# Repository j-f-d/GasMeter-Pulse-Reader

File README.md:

# GasMeter Pulse Reader

This project was forked from https://github.com/optoisolated/GasMeter-Pulse-Reader with the intention of providing the correct MQTT topics, such that it will work with the MQTT integration for https://www.home-assistant.io/ with the minimum of fuss.

I use a nodemocuv2 for monitoring at the moment, rather than the hardware created by @MakerMeik and @optoisolated so the pin I use is different (GPIO14 on D5 instead of GPIO9 or GPIO3). If you want to make the hardware, then you'll need to change this.

The mosquitto server is "mosquitto.home" and the device will look for that name using the DNS server provided by the DHCP configuration. The credentials used are stored in your secrets.h file. I add an entry in my DNS server, such that mosquitto.home redirects to the server which is running the mosquitto service.

The homeassistant MQTT integration is configured for the same server and when reloaded should see a new gas_meter device, which provides 2 entities. The gas_consumption entity is suitable for use with the energy dash board. The gas_flow_rate entity I use to determine how much gas is being used at any given moment.

This schematic and PCB layout will allow you to build, read, tally and report on a standard Pulse-Type Gas and Water Meters. Each trigger event consists of 10L of Gas consumed. This device has been confirmed compatible with the following meters:

* Gameco Model 750 Gas Meter (10L/impulse)

This project was forked from MakerMeik's Gasmeter_with_reed project and has been updated to be completely self-contained, self-powered (or direct powered) and has hardware debounce using a Schmitt trigger.

Here you will find all the files you need to build ESP-01 microcontroller and a reed switch to read your Krom-Schröder gas meter electronically.  

## Links
* MakerMeik's original Project video: https://youtu.be/i9hPf0uNzFE
* Thingiverse - 3D-Model of the case: https://www.thingiverse.com/thing:5338232

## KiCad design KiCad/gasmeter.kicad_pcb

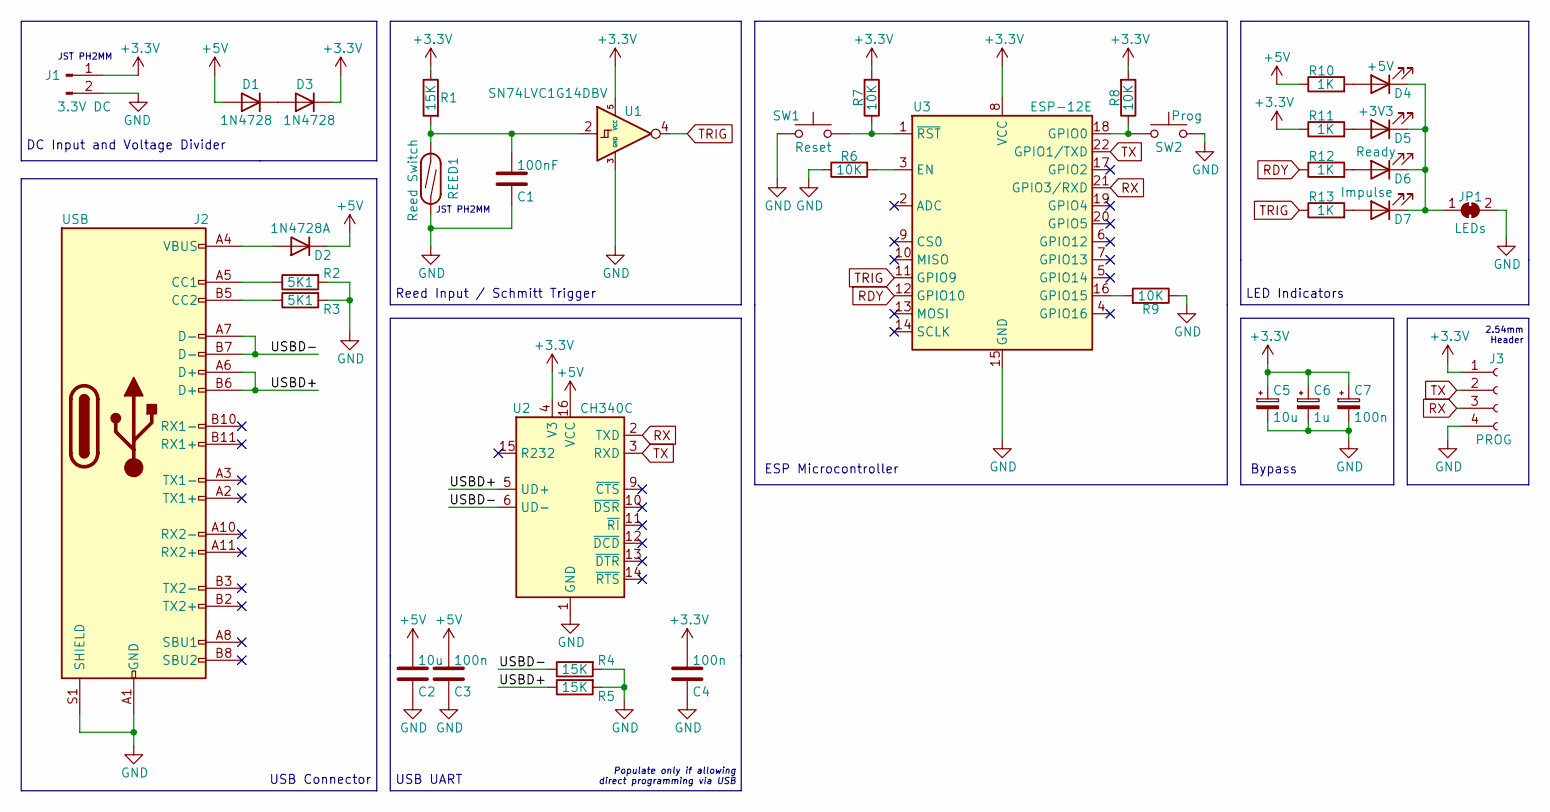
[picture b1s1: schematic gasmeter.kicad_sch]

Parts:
C1: 100nF; C_0805_2012Metric_Pad1.18x1.45mm_HandSolder
C2, C5: 10u; C_0805_2012Metric_Pad1.18x1.45mm_HandSolder
C3, C4, C7: 100n; C_0805_2012Metric_Pad1.18x1.45mm_HandSolder
C6: 1u; C_0805_2012Metric_Pad1.18x1.45mm_HandSolder
D1, D3: 1N4728; D_0805_2012Metric_Pad1.15x1.40mm_HandSolder
D2: 1N4728A; D_0805_2012Metric_Pad1.15x1.40mm_HandSolder
D4: +5V; LED_0805_2012Metric_Pad1.15x1.40mm_HandSolder
D5: +3V3; LED_0805_2012Metric_Pad1.15x1.40mm_HandSolder
D6: Ready; LED_0805_2012Metric_Pad1.15x1.40mm_HandSolder
D7: Impulse; LED_0805_2012Metric_Pad1.15x1.40mm_HandSolder
J1: 3.3V DC; JST_PH_B2B-PH-K_1x02_P2.00mm_Vertical
J2: USB; USB_C_Receptacle_Amphenol_12401548E4-2A
J3: PROG; PinHeader_1x04_P2.54mm_Vertical
JP1: LEDs; SolderJumper-2_P1.3mm_Bridged_Pad1.0x1.5mm
R1, R4, R5: 15K; R_0805_2012Metric_Pad1.20x1.40mm_HandSolder
R2, R3: 5K1; R_0805_2012Metric_Pad1.20x1.40mm_HandSolder
R6, R7, R8, R9: 10K; R_0805_2012Metric_Pad1.20x1.40mm_HandSolder
R10, R11, R12, R13: 1K; R_0805_2012Metric_Pad1.20x1.40mm_HandSolder
REED1: Reed Switch; JST_PH_B2B-PH-K_1x02_P2.00mm_Vertical
SW1: Reset; SW_SPST_EVQP2
SW2: Prog; SW_SPST_EVQP2
U1: SN74LVC1G14DBV; SOT-23-5
U2: CH340C; SOIC-16_3.9x9.9mm_P1.27mm
U3: ESP-12E

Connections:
+3V3: C4.2, C5.1, C6.1, C7.1, D3.1 (K), J1.1, J3.1, R1.1, R7.2, R8.2, R11.1, U1.5 (VCC), U2.4 (V3), U3.8 (VCC)
/USBD+: J2.A6 (D+), J2.B6 (D+), R5.1, U2.5 (UD+)
/USBD-: J2.A7 (D-), J2.B7 (D-), R4.1, U2.6 (UD-)
GND: C1.1, C2.1, C3.1, C4.1, C5.2, C6.2, C7.2, J1.2, J2.A1 (GND), J2.A12 (GND), J2.B1 (GND), J2.B12 (GND), J2.S1 (SHIELD), J3.4, JP1.2 (B), R2.2, R3.2, R4.2, R5.2, R6.1, R9.1, REED1.1, SW1.1, SW2.2, U1.3 (GND), U2.1 (GND), U3.15 (GND)
unnamed: C1.2, R1.2, REED1.2, U1.2
unnamed: D1.1 (K), D3.2 (A)
unnamed: D4.1 (K), D5.1 (K), D6.1 (K), D7.1 (K), JP1.1 (A)
unnamed: D4.2 (A), R10.2
unnamed: D5.2 (A), R11.2
unnamed: D6.2 (A), R12.2
unnamed: D7.2 (A), R13.2
unnamed: J2.A5 (CC1), R2.1
unnamed: J2.B5 (CC2), R3.1
unnamed: R6.2, U3.3 (EN)
unnamed: R7.1, SW1.2, U3.1 (~RST)
unnamed: R8.1, SW2.1, U3.18 (GPIO0)
unnamed: R9.2, U3.16 (GPIO15)
RDY: R12.1, U3.12 (GPIO10)
RX: J3.3, U2.2 (TXD), U3.21 (GPIO3/RXD)
TRIG: R13.1, U1.4, U3.11 (GPIO9)
TX: J3.2, U2.3 (RXD), U3.22 (GPIO1/TXD)

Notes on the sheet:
LED Indicators
JST PH2MM
USB Connector
Reed Input / Schmitt Trigger
ESP Microcontroller
2.54mm Header
DC Input and Voltage Divider
USB UART
Populate only if allowing direct programming via USB
Bypass

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
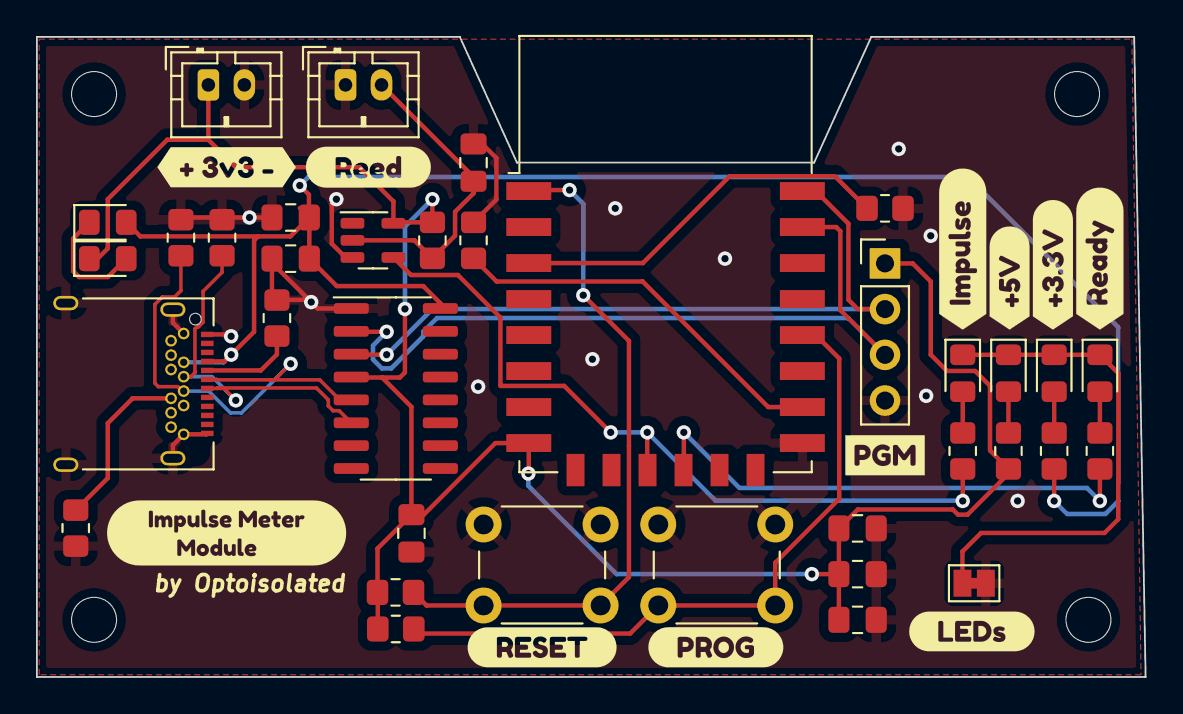
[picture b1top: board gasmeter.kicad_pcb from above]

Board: 2 copper layers, 61.6 x 35.6 mm, 47 parts (0 on the bottom side), 22 nets.

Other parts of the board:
kibuzzard-61B4AC1D: G***; kibuzzard-61B4AC1D
kibuzzard-61B4AC13: G***; kibuzzard-61B4AC13
kibuzzard-61B4AC28: G***; kibuzzard-61B4AC28
kibuzzard-61B4AC41: G***; kibuzzard-61B4AC41
kibuzzard-61B4AE0E: G***; kibuzzard-61B4AE0E
kibuzzard-61B4AE05: G***; kibuzzard-61B4AE05
kibuzzard-61B51C34: G***; kibuzzard-61B51C34
kibuzzard-61B51C69: G***; kibuzzard-61B51C69
kibuzzard-61B51CF9: G***; kibuzzard-61B51CF9
kibuzzard-61B51D56: G***; kibuzzard-61B51D56
kibuzzard-61B52BC4: G***; kibuzzard-61B52BC4

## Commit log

2021-12-10 Added Schmitt Trigger
    Modified the schematic to include a Schmitt trigger on the input reed switch, and tidied up the design.
2021-12-10 Cleaned up Schematic Layout
    Layout Cleanup, Added DC Input and protection. Now runs with 5V input.
2021-12-11 Refactored Design
    * Now runs using an ESP12E
    * LED Indicators added
    * Programming Header
    * Optional USB UART interface onboard
    * USB-C Power/Data (power-only if UART not populated)
    * Diode-based Voltage Divider
2021-12-11 Prototype PCB Layout
2021-12-12 Minor Update
2022-09-22 Fixed broken thingiverse link
2023-06-29 Hass.io Compatible version using NodeMCUv2
2023-06-30 Updated to introduce this version
2023-07-03 Modified to help diagnose mqtt connection
